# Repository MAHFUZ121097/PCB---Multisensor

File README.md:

# PCB---Multisensor

## Overview

**EcIPoTH** is a custom-designed Printed Circuit Board (PCB) intended for the acquisition of multiple physiological signals. This versatile board integrates various sensors to measure and track vital parameters. It is designed for research and development in physiological signal monitoring, and can be easily adapted for a wide range of applications.

### PCB Image

### Sensors Included:
1. **Ec** - Electrocardiogram (ECG) Sensor
2. **I** - Inertial Measurement Unit (IMU) Sensor
3. **Po** - Pulse Oximeter Sensor
4. **TH** - Temperature and Humidity Sensor

### Key Features:
- Multisensor PCB layout (2-layer) for real-time physiological data acquisition
- Operating voltage: ~3.3 V
- Compact dimensions: 60 mm x 50 mm
- Modular design for easy integration into wearable or portable devices
- Designed for medical and research applications

### Design Environment:
- KiCad EDA 6.0.10

## Dimensions

- **PCB Size:** 60 mm x 50 mm

## Sensors Overview

### ECG Sensor (Ec)
- AD8232 chip: Captures electrical activity of the heart, includes instrumentation amplifier.
  
### IMU Sensor (I)
- MPU6050 chip: Inertial measurement unit (IMU) to capture breathing patterns, includes accelerometer and gyroscope.

### Pulse Oximeter Sensor (Po)
- Max30101 chip: Captures LED data to measure pulse rate and oxygen saturation, includes infrared (IR) and red LED.

### Temperature and Humidity Sensor (TH)
- Si7021 chip: Records core body temperature and humidity measurements.

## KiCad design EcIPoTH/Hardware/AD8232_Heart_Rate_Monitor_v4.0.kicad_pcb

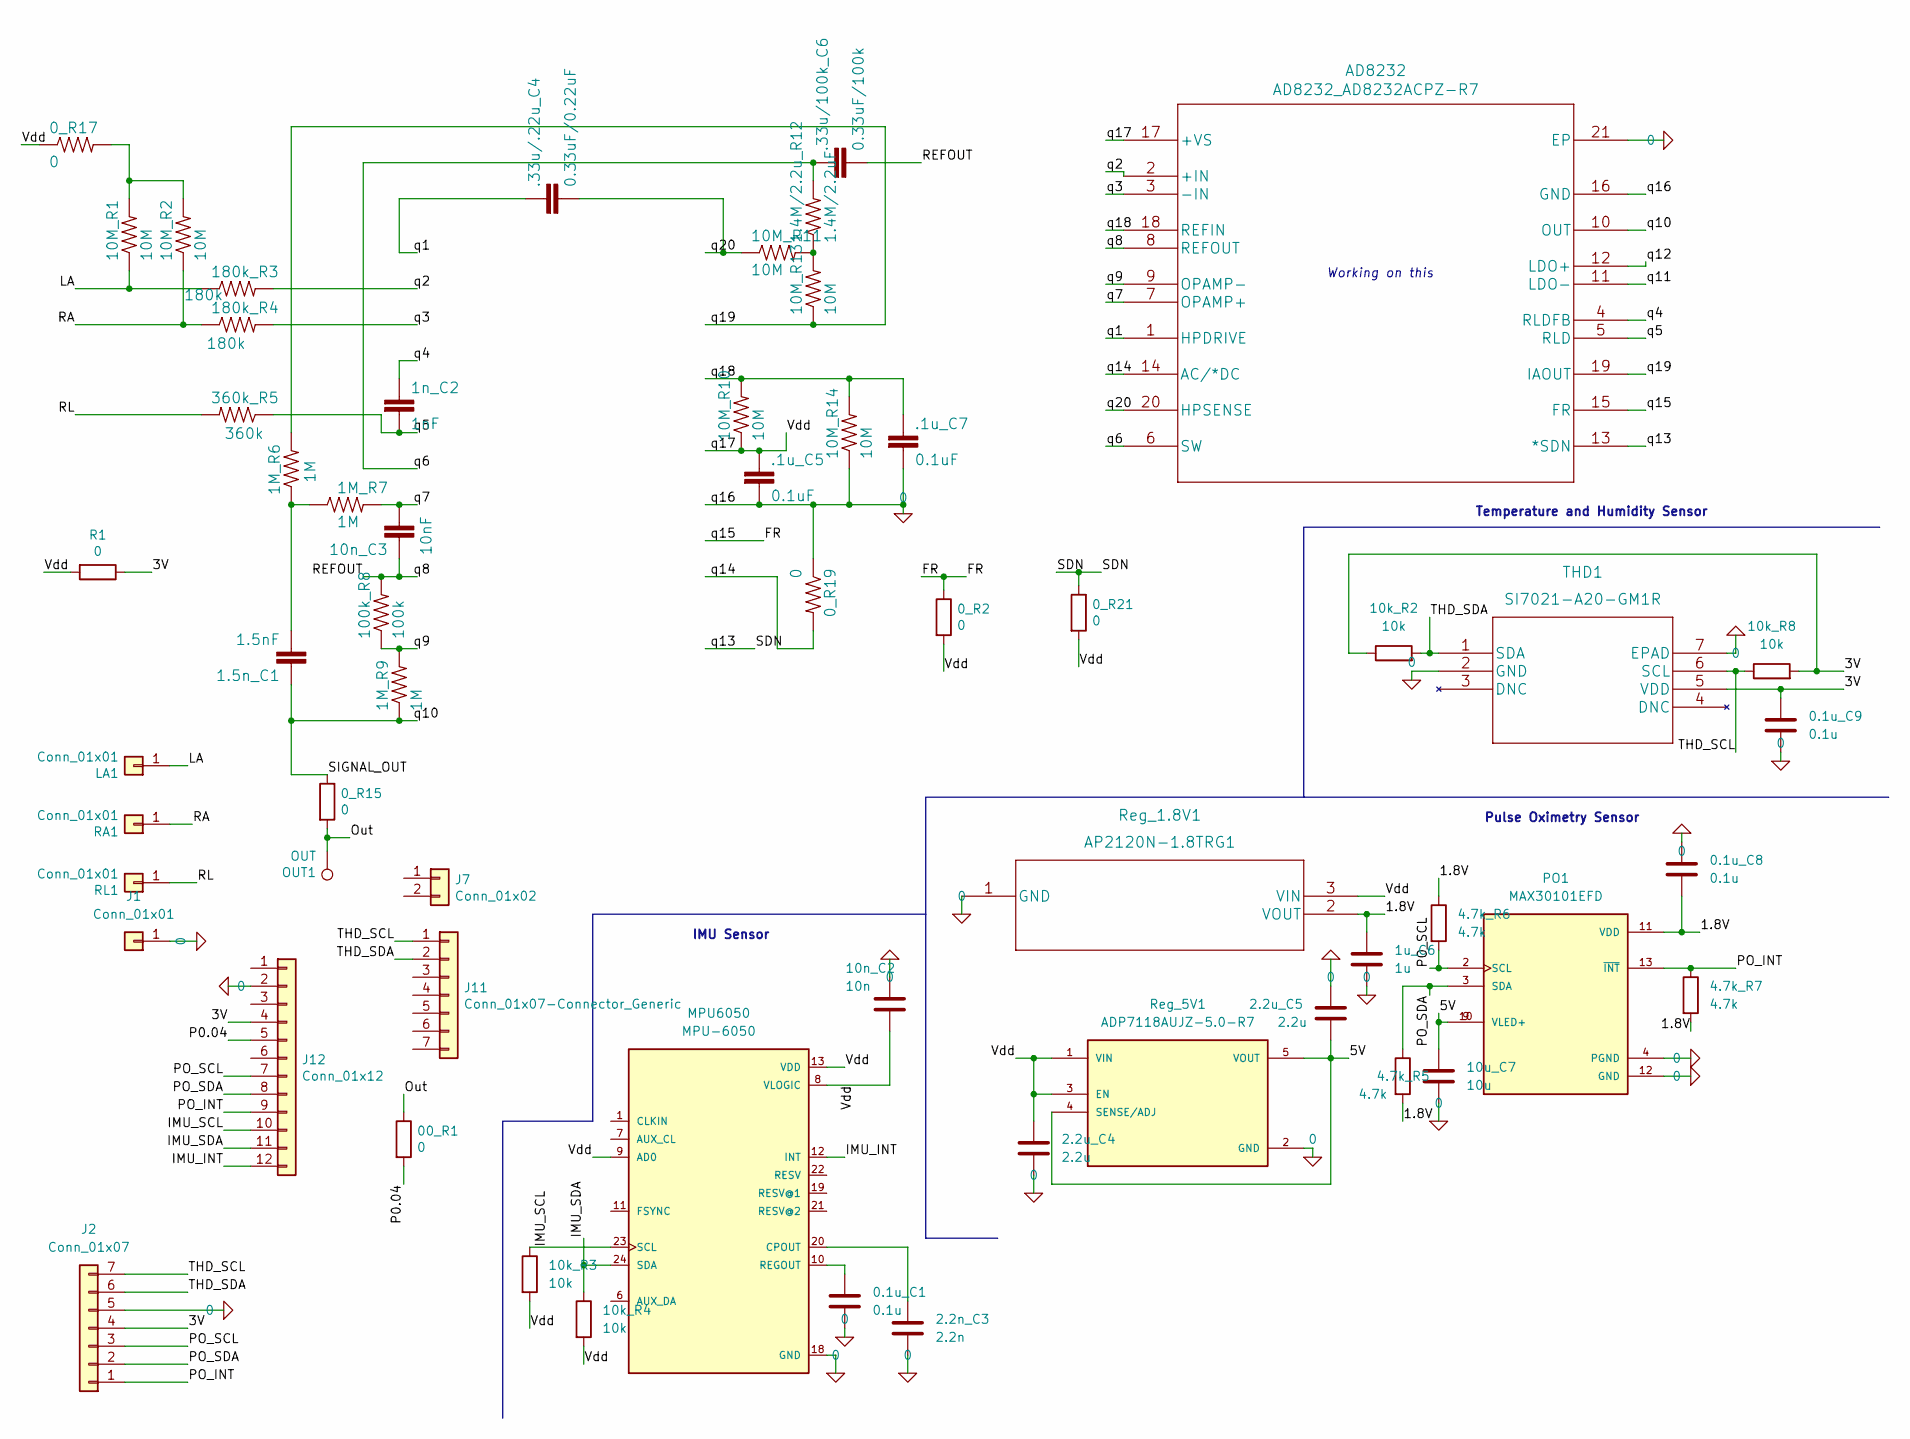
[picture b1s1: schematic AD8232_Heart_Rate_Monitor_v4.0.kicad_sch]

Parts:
0.1u_C1, 0.1u_C8, 0.1u_C9: 0.1u; C_0603_1608Metric
00_R1, 0_R2, 0_R15, 0_R17, 0_R19, 0_R21: 0; R_0603_1608Metric
1.4M/2.2u_R12: 1.4M/2.2uF; R_0603_1608Metric
1.5n_C1: 1.5nF; C_0603_1608Metric
1M_R6, 1M_R7, 1M_R9: 1M; R_0603_1608Metric
1n_C2: 1nF; C_0603_1608Metric
1u_C6: 1u; C_0603_1608Metric
2.2n_C3: 2.2n; C_0603_1608Metric
2.2u_C4, 2.2u_C5: 2.2u; C_0603_1608Metric
4.7k_R5, 4.7k_R6, 4.7k_R7: 4.7k; R_0603_1608Metric
10M_R1, 10M_R2, 10M_R10, 10M_R11, 10M_R13, 10M_R14: 10M; R_0603_1608Metric
10k_R2, 10k_R3, 10k_R4, 10k_R8: 10k; R_0603_1608Metric
10n_C2: 10n; C_0603_1608Metric
10n_C3: 10nF; C_0603_1608Metric
10u_C7: 10u; C_0603_1608Metric
100k_R8: 100k; R_0603_1608Metric
180k_R3, 180k_R4: 180k; R_0603_1608Metric
360k_R5: 360k; R_0603_1608Metric
.1u_C5, .1u_C7: 0.1uF; C_0603_1608Metric
.33u/100k_C6: 0.33uF/100k; C_0603_1608Metric
.33u/.22u_C4: 0.33uF/0.22uF; C_0603_1608Metric
AD8232: AD8232_AD8232ACPZ-R7; QFN-20-1EP_4x4mm_P0.5mm_EP2.5x2.5mm
J1: Conn_01x01; PinHeader_1x01_P2.54mm_Vertical
J2: Conn_01x07; PinHeader_1x07_P2.54mm_Vertical
J7: Conn_01x02; PinHeader_1x02_P2.54mm_Vertical
J11: Conn_01x07-Connector_Generic; PinHeader_1x07_P2.54mm_Vertical
J12: Conn_01x12; PinHeader_1x12_P2.54mm_Vertical
LA1: Conn_01x01; PinHeader_1x01_P2.54mm_Vertical
MPU6050: MPU-6050; MPU-6050-400X400X95-24N; PARTREV 3.4
OUT1: OUT; PinHeader_1x01_P1.00mm_Vertical
PO1: MAX30101EFD; PSON80P560X330X165-14N; PARTREV 2
R1: 0; R_0603_1608Metric
RA1: Conn_01x01; PinHeader_1x01_P2.54mm_Vertical
RL1: Conn_01x01; PinHeader_1x01_P2.54mm_Vertical
Reg_1.8V1: AP2120N-1.8TRG1
Reg_5V1: ADP7118AUJZ-5.0-R7; ADP_5V_Reg; PARTREV E
THD1: SI7021-A20-GM1R

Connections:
0: 0.1u_C1.2, 0.1u_C8.1, 0.1u_C9.2, 0_R19.1, 1u_C6.2, 2.2n_C3.2, 2.2u_C4.2, 2.2u_C5.1, 10M_R14.1, 10n_C2.1, 10u_C7.2, .1u_C5.2, .1u_C7.2, AD8232.16 (GND), AD8232.21 (EP), J1.1, J2.5, J12.2, MPU6050.18 (GND), PO1.4 (PGND), PO1.12 (GND), Reg_1.8V1.1 (GND), Reg_5V1.2 (GND), THD1.2 (GND), THD1.7 (EPAD)
/1.8V: 0.1u_C8.2, 1u_C6.1, 4.7k_R5.2, 4.7k_R6.1, 4.7k_R7.2, PO1.11 (VDD), Reg_1.8V1.2 (VOUT)
/3V: 0.1u_C9.1, 10k_R2.1, 10k_R8.2, J2.4, J12.4, R1.1, THD1.5 (VDD)
/5V: 2.2u_C5.2, 10u_C7.1, PO1.9 (VLED+), PO1.10 (VLED+), Reg_5V1.4 (SENSE/ADJ), Reg_5V1.5 (VOUT)
/FR: 0_R2.1, AD8232.15 (FR)
/IMU_INT: J12.12, MPU6050.12 (INT)
/IMU_SCL: 10k_R3.1, J12.10, MPU6050.23 (SCL)
/IMU_SDA: 10k_R4.1, J12.11, MPU6050.24 (SDA)
/LA: 10M_R1.1, 180k_R3.1, LA1.1
/Out: 00_R1.1, 0_R15.2, OUT1.1
/P0.04: 00_R1.2, J12.5
/PO_INT: 4.7k_R7.1, J2.1, J12.9, PO1.13 (~INT)
/PO_SCL: 4.7k_R6.2, J2.3, J12.7, PO1.2 (SCL)
/PO_SDA: 4.7k_R5.1, J2.2, J12.8, PO1.3 (SDA)
/RA: 10M_R2.1, 180k_R4.1, RA1.1
/REFOUT: 10n_C3.1, 100k_R8.2, .33u/100k_C6.2, AD8232.8 (REFOUT)
/RL: 360k_R5.2, RL1.1
/SDN: 0_R21.1, AD8232.13 (*SDN)
/SIGNAL_OUT: 0_R15.1, 1.5n_C1.1, 1M_R9.1, AD8232.10 (OUT)
/THD_SCL: 10k_R8.1, J2.7, J11.1, THD1.6 (SCL)
/THD_SDA: 10k_R2.2, J2.6, J11.2, THD1.1 (SDA)
/Vdd: 0_R2.2, 0_R17.1, 0_R21.2, 2.2u_C4.1, 10M_R10.1, 10k_R3.2, 10k_R4.2, 10n_C2.2, .1u_C5.1, AD8232.17 (+VS), MPU6050.8 (VLOGIC), MPU6050.9 (AD0), MPU6050.13 (VDD), R1.2, Reg_1.8V1.3 (VIN), Reg_5V1.1 (VIN), Reg_5V1.3 (EN)
/q1: .33u/.22u_C4.1, AD8232.1 (HPDRIVE)
/q2: 180k_R3.2, AD8232.2 (+IN)
/q3: 180k_R4.2, AD8232.3 (-IN)
/q4: 1n_C2.1, AD8232.4 (RLDFB)
/q5: 1n_C2.2, 360k_R5.1, AD8232.5 (RLD)
/q6: 1.4M/2.2u_R12.2, .33u/100k_C6.1, AD8232.6 (SW)
/q7: 1M_R7.2, 10n_C3.2, AD8232.7 (OPAMP+)
/q9: 1M_R9.2, 100k_R8.1, AD8232.9 (OPAMP-)
/q11: AD8232.11 (LDO-)
/q12: AD8232.12 (LDO+)
/q14: 0_R19.2, AD8232.14 (AC/*DC)
/q18: 10M_R10.2, 10M_R14.2, .1u_C7.1, AD8232.18 (REFIN)
/q19: 1M_R6.2, 10M_R13.1, AD8232.19 (IAOUT)
/q20: 10M_R11.1, .33u/.22u_C4.2, AD8232.20 (HPSENSE)
unnamed: 0.1u_C1.1, MPU6050.10 (REGOUT)
unnamed: 0_R17.2, 10M_R1.2, 10M_R2.2
unnamed: 1.4M/2.2u_R12.1, 10M_R11.2, 10M_R13.2
unnamed: 1.5n_C1.2, 1M_R6.1, 1M_R7.1
unnamed: 2.2n_C3.1, MPU6050.20 (CPOUT)

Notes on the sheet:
Pulse Oximetry Sensor
IMU Sensor
Temperature and Humidity Sensor
Working on this

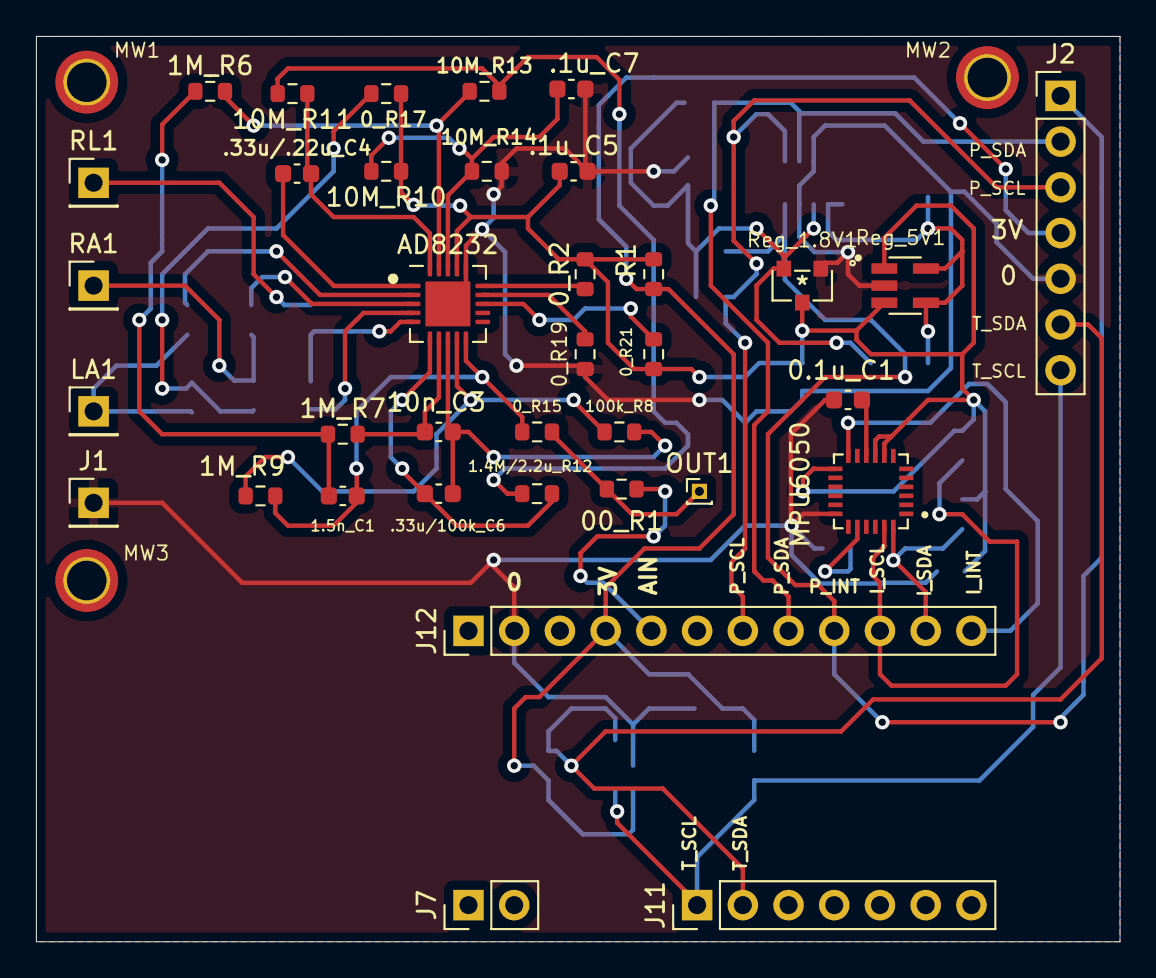
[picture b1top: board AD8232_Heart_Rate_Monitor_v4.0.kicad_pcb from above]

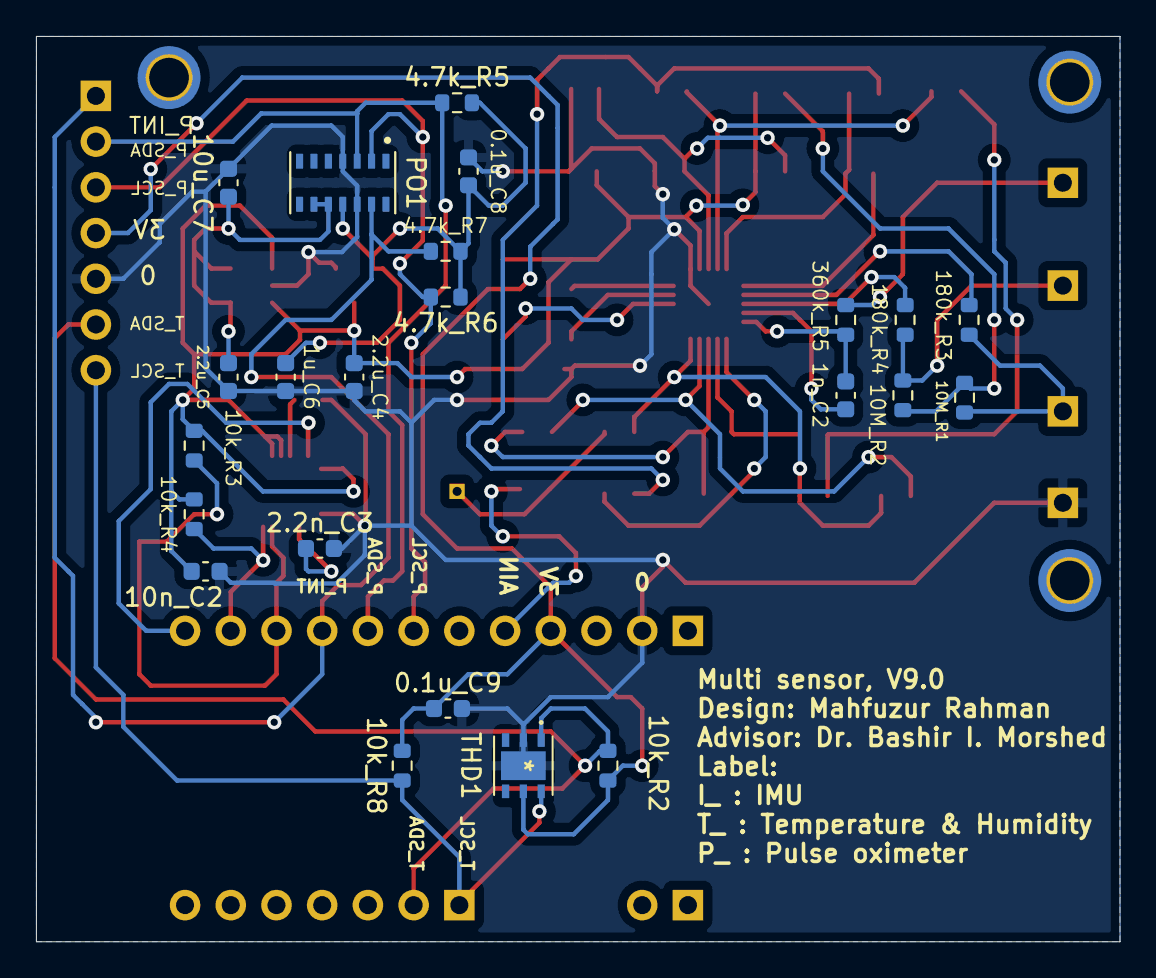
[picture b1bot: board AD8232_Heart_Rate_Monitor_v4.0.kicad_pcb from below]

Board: 2 copper layers, 60.2 x 50.3 mm, 62 parts (23 on the bottom side), 39 nets.

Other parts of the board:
MW1, MW2, MW3: MountingHole_2.2mm_M2_ISO7380_Pad_TopBottom

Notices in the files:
parts and their libraries:
Copyright 2021 Accelerated Designs. All rights reserved.
